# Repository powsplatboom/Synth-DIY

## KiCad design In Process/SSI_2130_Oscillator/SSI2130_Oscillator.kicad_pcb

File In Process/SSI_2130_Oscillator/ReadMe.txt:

VCO based on the SSI 2130 by sound semiconductor. Not yet spun, will update when the board has been spun.

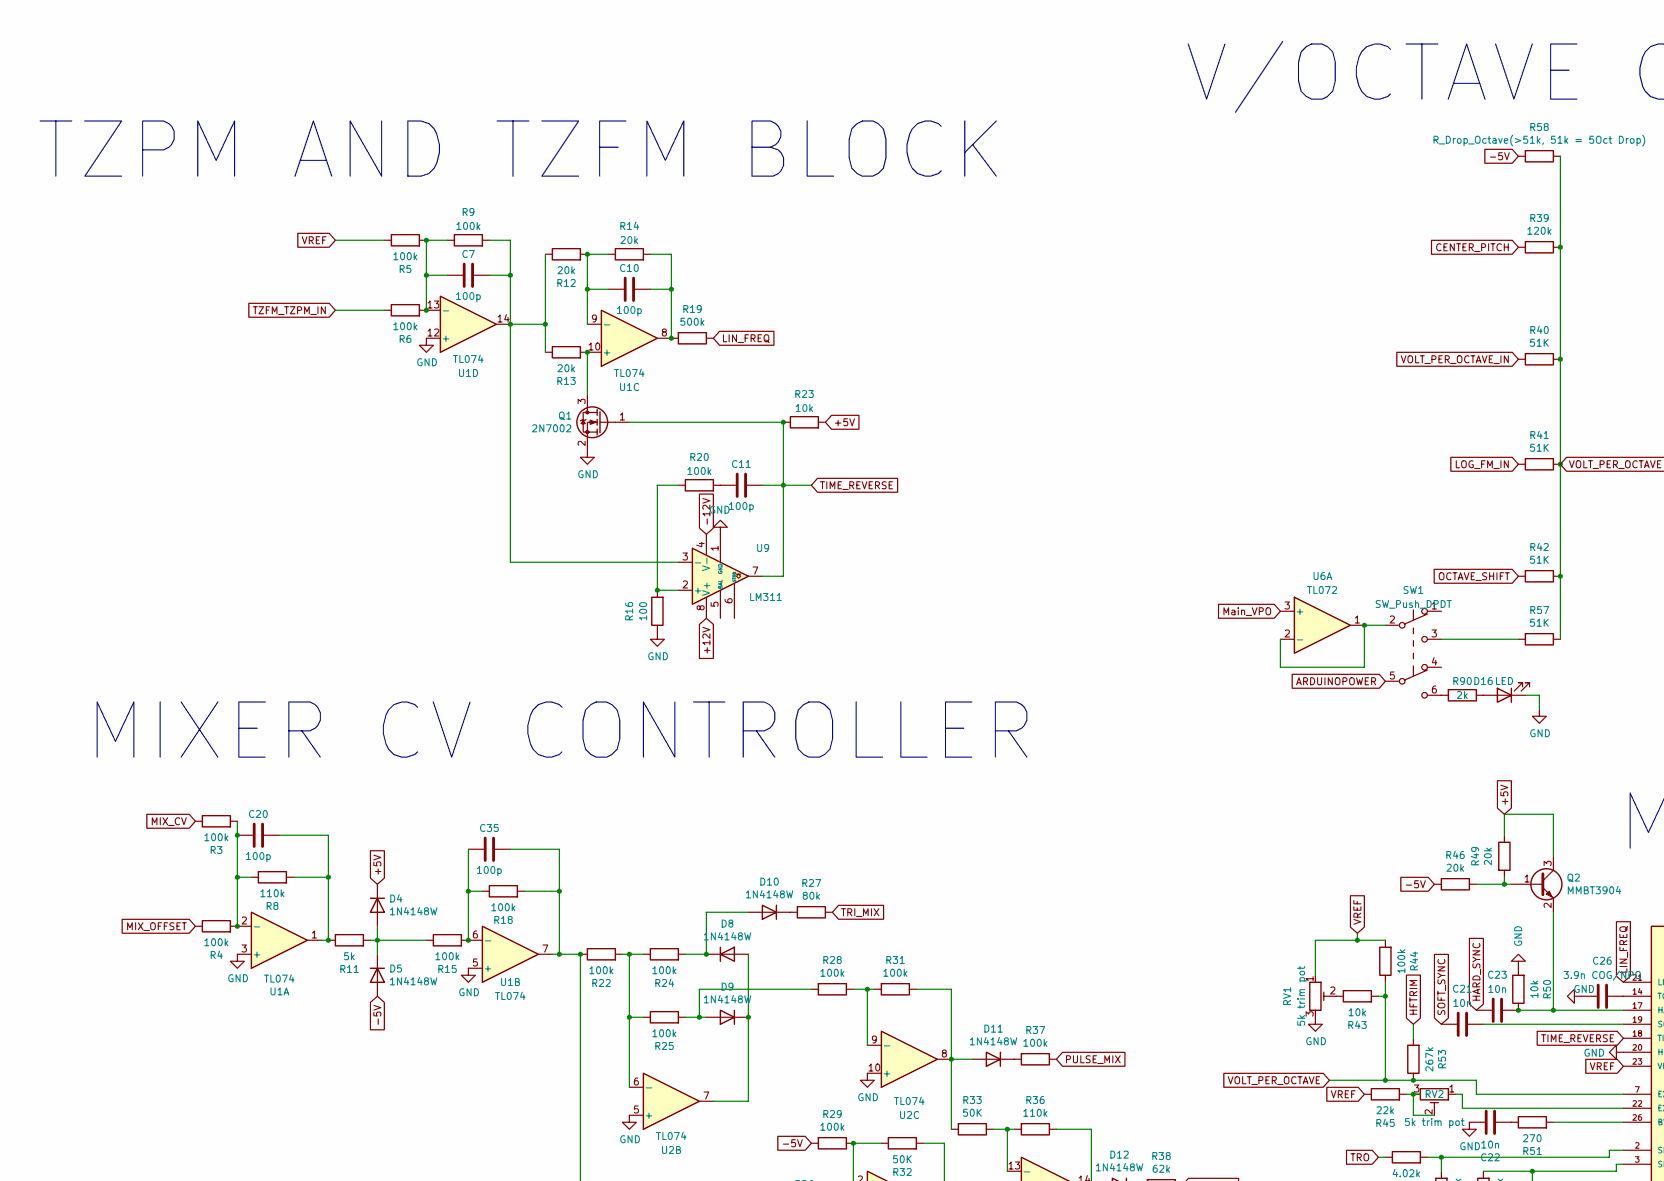
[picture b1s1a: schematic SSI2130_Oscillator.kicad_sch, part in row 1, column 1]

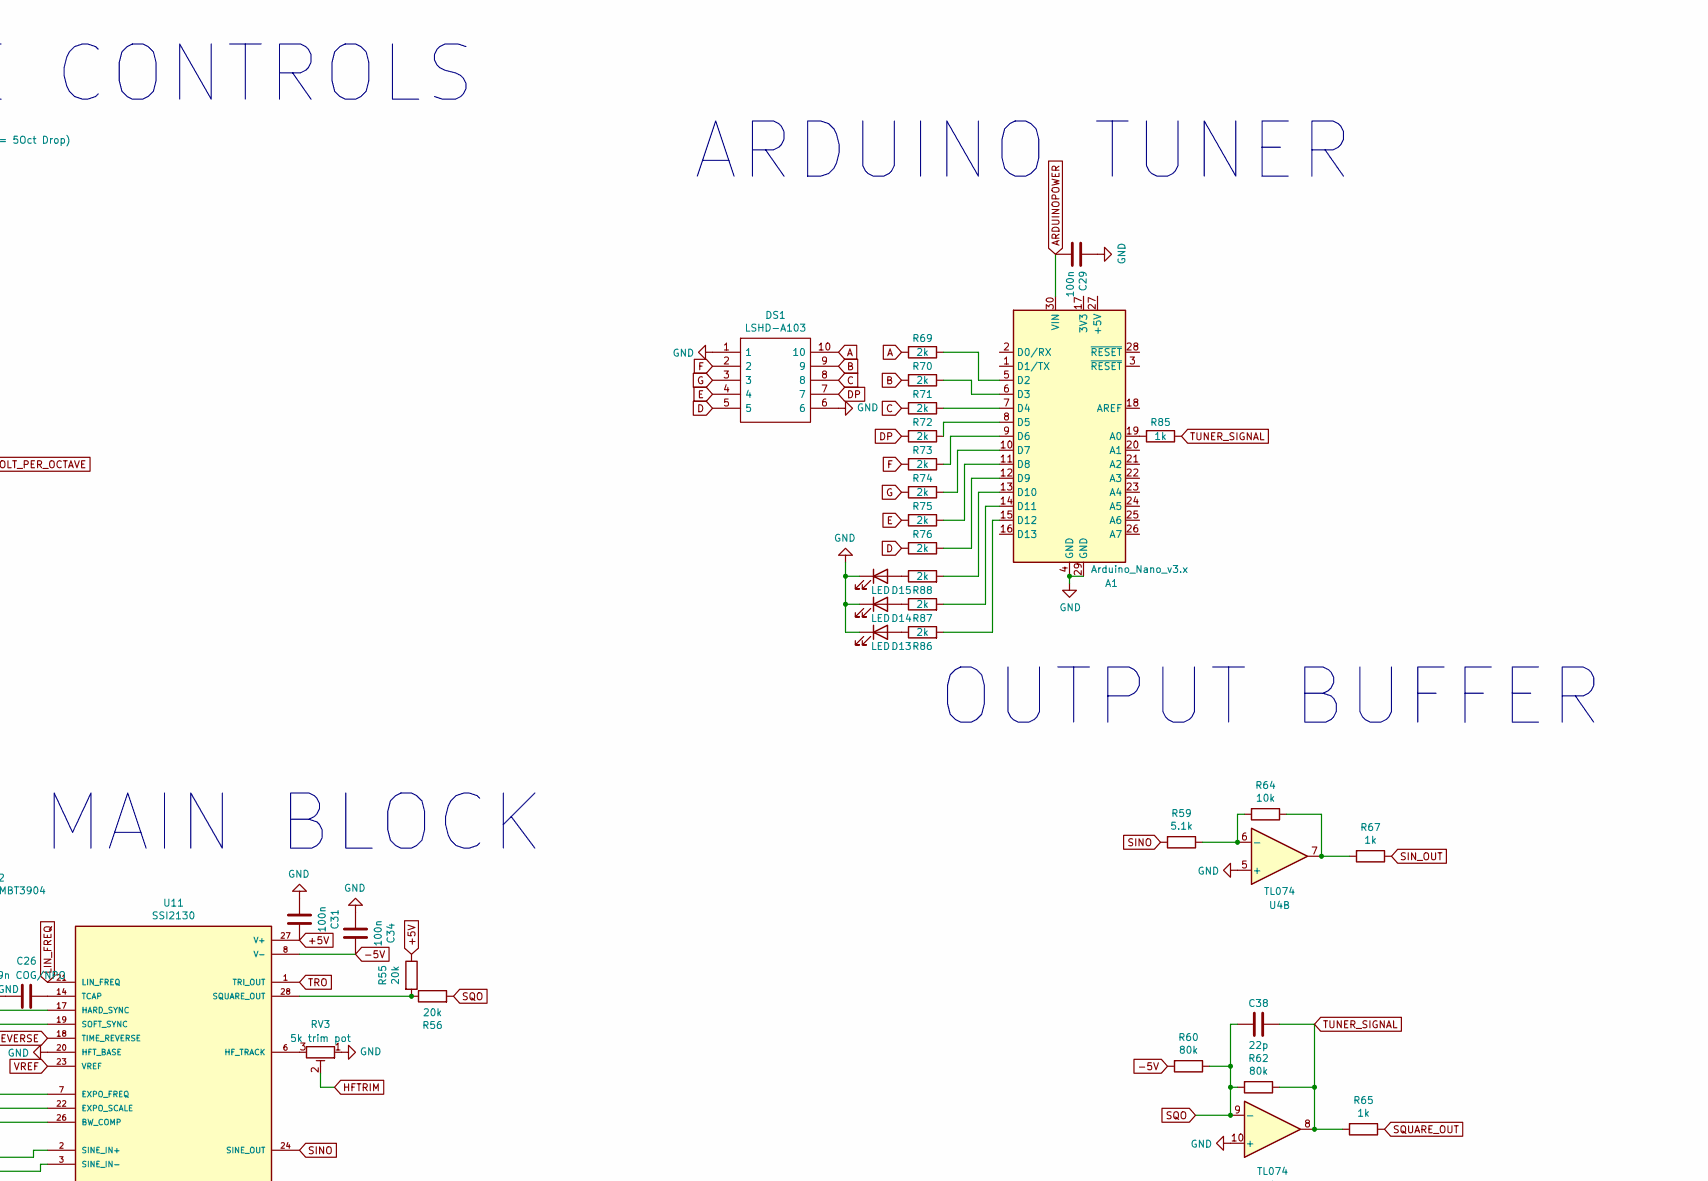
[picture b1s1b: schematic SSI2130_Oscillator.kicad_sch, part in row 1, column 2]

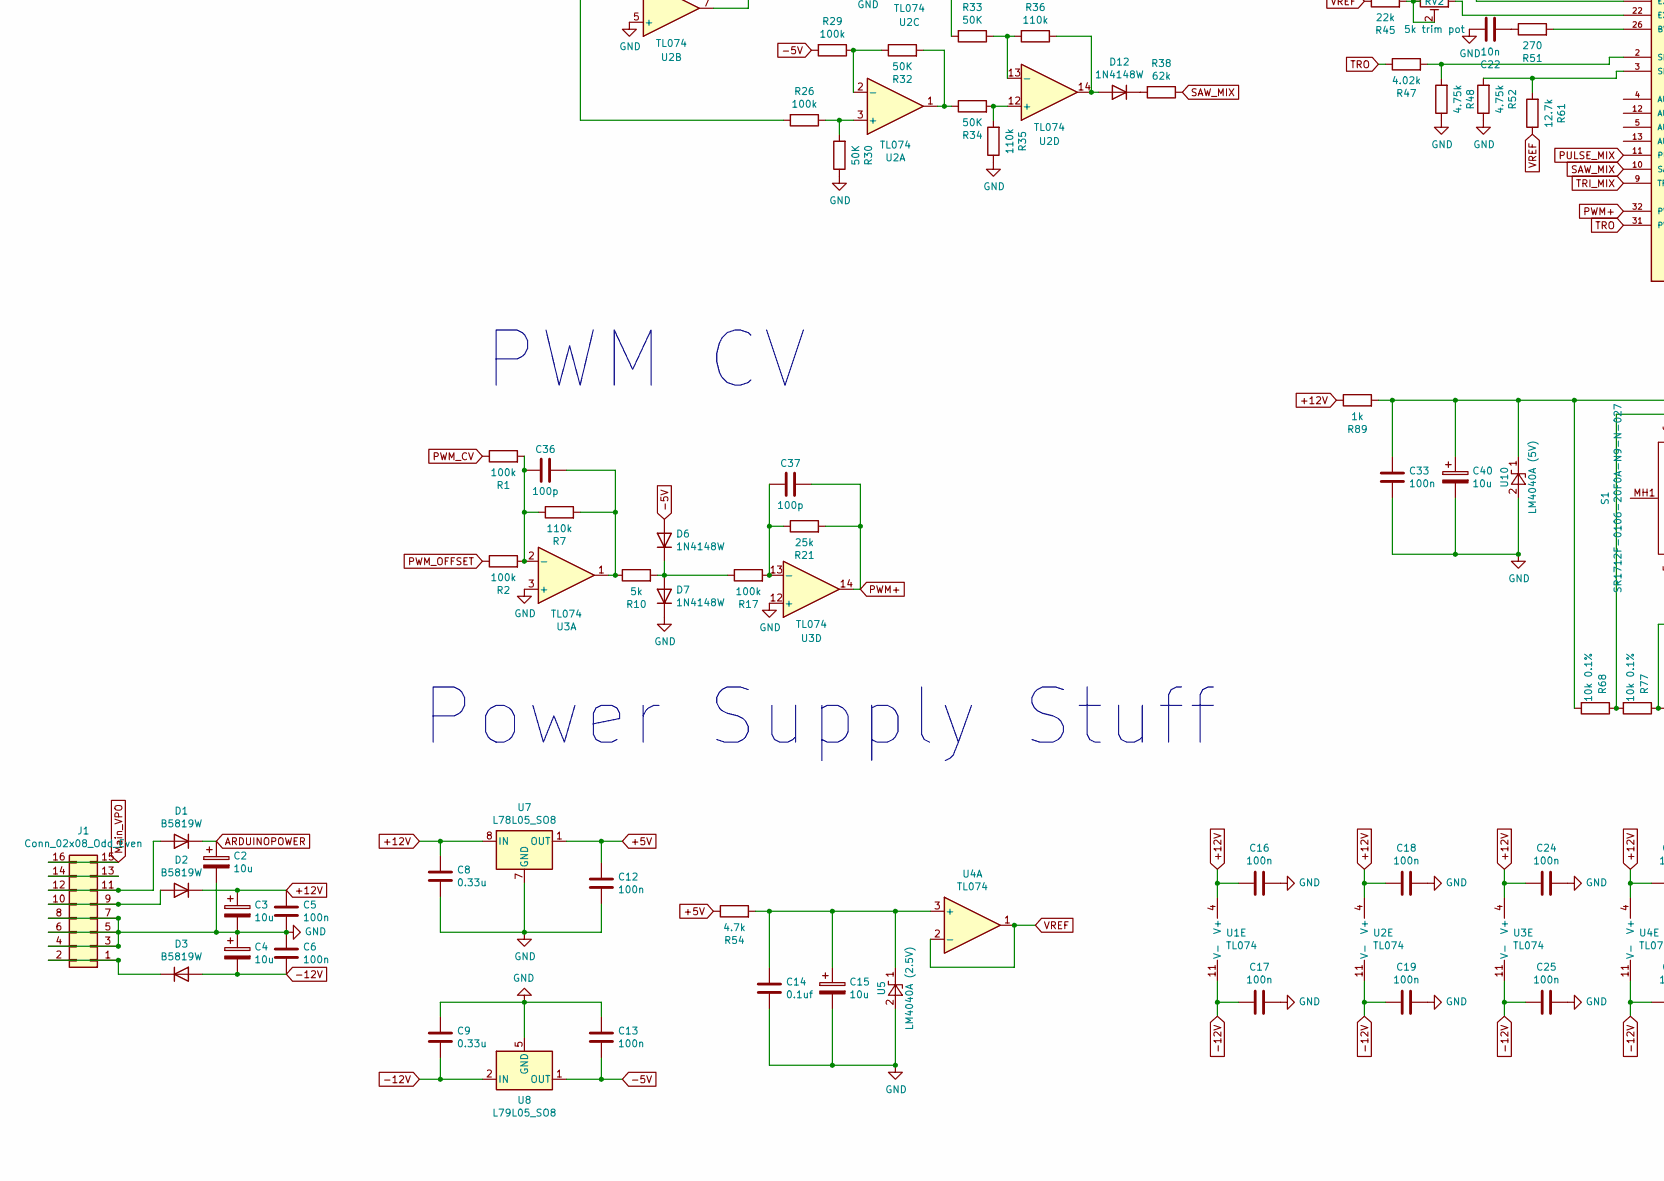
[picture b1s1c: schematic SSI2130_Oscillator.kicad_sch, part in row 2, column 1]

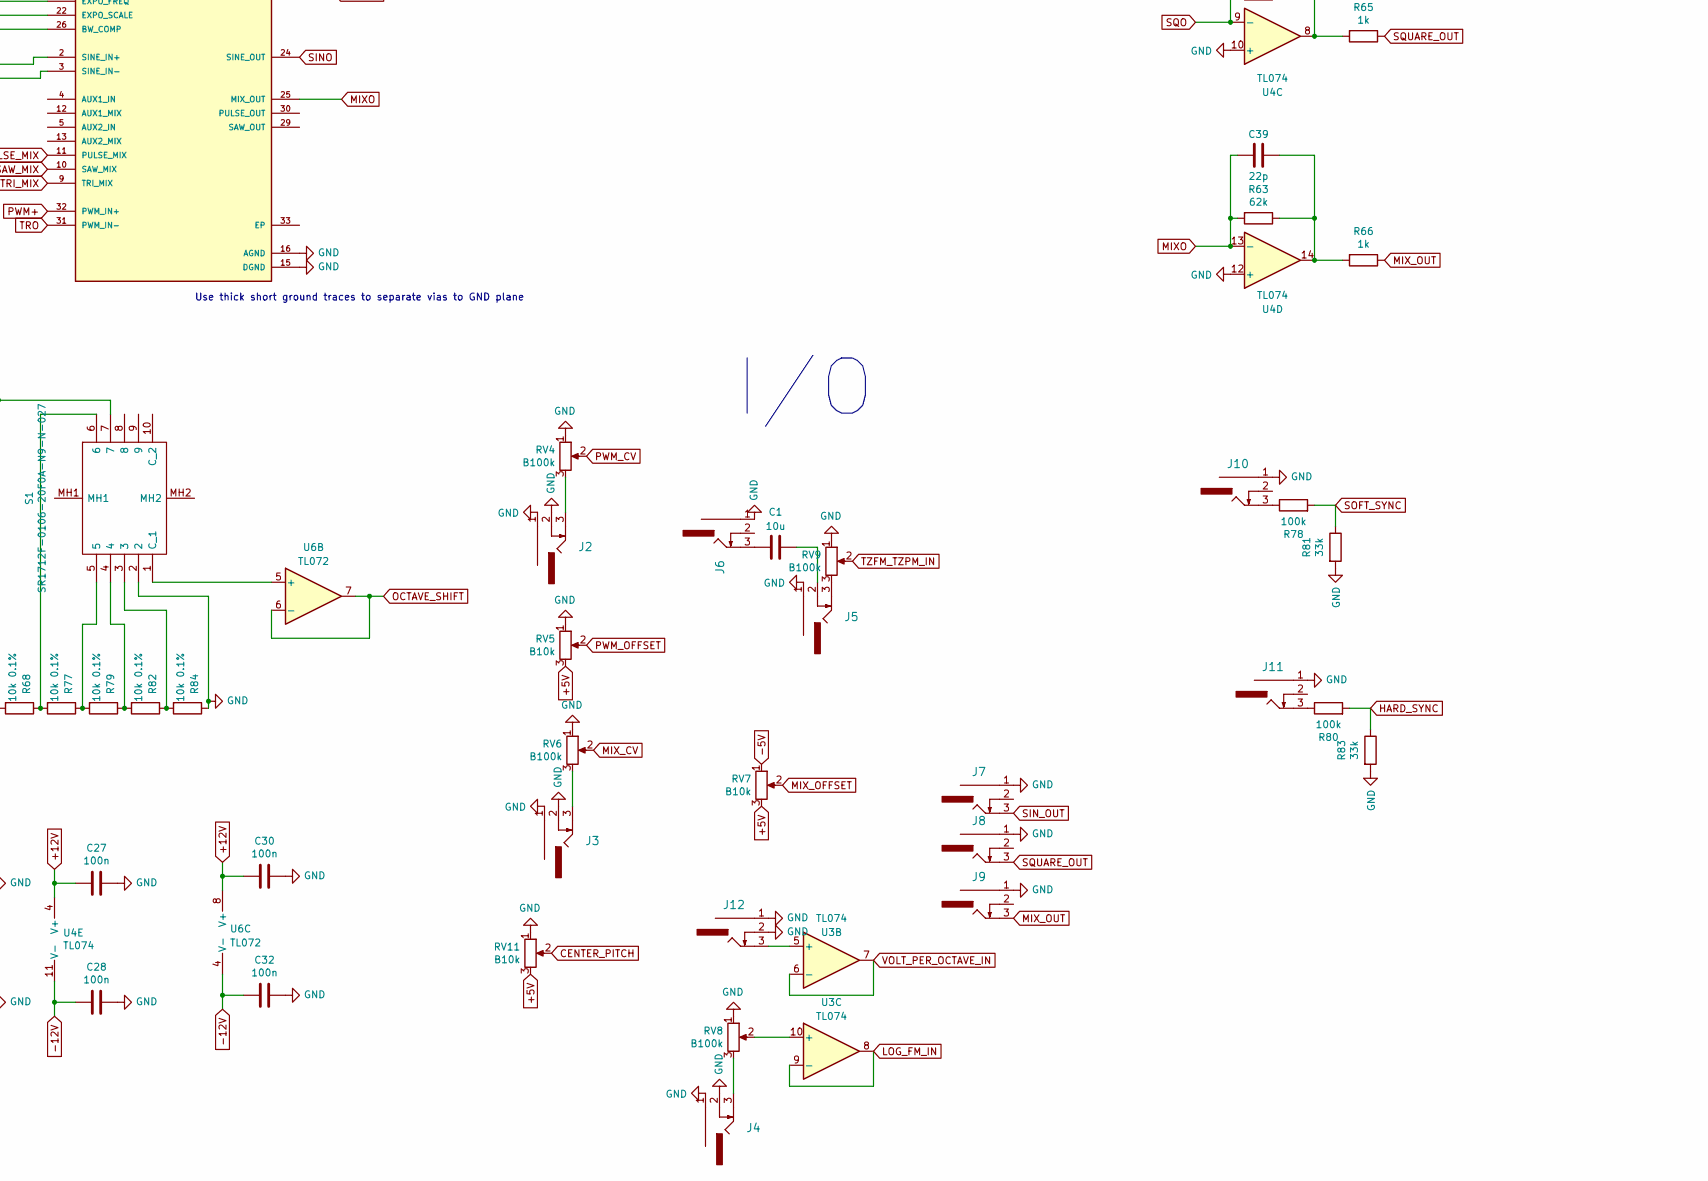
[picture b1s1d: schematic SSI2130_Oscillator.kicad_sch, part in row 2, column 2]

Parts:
A1: Arduino_Nano_v3.x; Arduino_Nano
C1: 10u; C_0603_1608Metric
C2, C3, C4, C15, C40: 10u; CP_Elec_4x5.3
C5, C6, C12, C13, C16, C17, C18, C19, C24, C25, C27, C28, C29, C30, C31, C32, C33, C34: 100n; C_0603_1608Metric
C7, C10, C11, C20, C35, C36, C37: 100p; C_0603_1608Metric
C8, C9: 0.33u; C_0603_1608Metric
C14: 0.1uf; C_0603_1608Metric
C21, C22, C23: 10n; C_0603_1608Metric
C26: 3.9n COG/NPO; C_0603_1608Metric
C38, C39: 22p; C_0603_1608Metric
D1, D2, D3: B5819W; D_SOD-123
D4, D5, D6, D7, D8, D9, D10, D11, D12: 1N4148W; D_SOD-123
D13, D14, D15, D16: LED; LED_0805_2012Metric
DS1: LSHD-A103; DIPS508W50P254L1270H609Q10N; Manufacturer_Part_Number LSHD-A101; Mouser Part Number 859-LSHD-A101
J1: Conn_02x08_Odd_Even; IDC-Header_2x08_P2.54mm_Vertical
J2, J3, J4, J5, J6, J7, J8, J9, J10, J11, J12: PJ301_THONKICONN; PJ-3001_Mono_Phone
Q1: 2N7002; SOT-23
Q2: MMBT3904; SOT-23
R1, R2, R3, R4, R5, R6, R9, R15, R17, R18, R20, R22, R24, R25, R26, R28, R29, R31, R37, R44, R78, R80: 100k; R_0603_1608Metric
R7, R8, R35, R36: 110k; R_0603_1608Metric
R10, R11: 5k; R_0603_1608Metric
R12, R13, R14, R46, R49, R55, R56: 20k; R_0603_1608Metric
R16: 100; R_0603_1608Metric
R19: 500k; R_0603_1608Metric
R21: 25k; R_0603_1608Metric
R23, R43, R50, R64: 10k; R_0603_1608Metric
R27, R60, R62: 80k; R_0603_1608Metric
R30, R32, R33, R34: 50K; R_0603_1608Metric
R38, R63: 62k; R_0603_1608Metric
R39: 120k; R_0603_1608Metric
R40, R41, R42, R57: 51K; R_0603_1608Metric
R45: 22k; R_0603_1608Metric
R47: 4.02k; R_0603_1608Metric
R48, R52: 4.75k; R_0603_1608Metric
R51: 270; R_0603_1608Metric
R53: 267k; R_0603_1608Metric
R54: 4.7k; R_0603_1608Metric
R58: R_Drop_Octave(>51k, 51k = 5Oct Drop); R_0603_1608Metric
R59: 5.1k; R_0603_1608Metric
R61: 12.7k; R_0603_1608Metric
R65, R66, R67, R85, R89: 1k; R_0603_1608Metric
R68, R77, R79, R82, R84: 10k 0.1%; R_0603_1608Metric
R69, R70, R71, R72, R73, R74, R75, R76, R86, R87, R88, R90: 2k; R_0603_1608Metric
R81, R83: 33k; R_0603_1608Metric
RV1, RV2, RV3: 5k trim pot; Potentiometer_Bourns_3296W_Vertical
RV4, RV6, RV8, RV9: B100k; Potentiometer_Alpha_RD901F-40-00D_Single_Vertical
RV5, RV7, RV11: B10k; Potentiometer_Alpha_RD901F-40-00D_Single_Vertical
S1: SR1712F-0106-20F0A-N9-N-027; SR1712F010620F0AN9N027; Manufacturer_Part_Number SR1712F-0106-20F0A-N9-N-027; Mouser Part Number 105-SR1712F-16NS
SW1: SW_Push_DPDT; DPDT Tayda Push Switch
U1, U2, U3, U4: TL074; SOIC-14_3.9x8.7mm_P1.27mm
U5: LM4040A (2.5V); SOT-23
U6: TL072; SO-8_3.9x4.9mm_P1.27mm
U7: L78L05_SO8; SOIC-8_3.9x4.9mm_P1.27mm
U8: L79L05_SO8; SOIC-8_3.9x4.9mm_P1.27mm
U9: LM311; SOIC-8_3.9x4.9mm_P1.27mm
U10: LM4040A (5V); SOT-23
U11: SSI2130; QFN-32-1EP_4x4mm_P0.4mm_EP2.9x2.9mm; PARTREV Rev. 2.4

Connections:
+5V: C12.1, C31.1, D4.1 (K), Q2.3 (C), R23.2, R49.1, R54.1, R55.1, RV5.3, RV7.3, RV11.3, U7.1 (OUT), U11.27 (V+)
+12V: C3.1, C5.1, C8.1, C16.2, C18.2, C24.2, C27.2, C30.2, D2.1 (K), R89.1, U1.4 (V+), U2.4 (V+), U3.4 (V+), U4.4 (V+), U6.8 (V+), U7.8 (IN), U9.8 (V+)
-5V: C13.2, C34.1, D5.2 (A), D6.2 (A), R29.2, R46.2, R58.2, R60.2, RV7.1, U8.1 (OUT), U11.8 (V-)
-12V: C4.2, C6.2, C9.2, C17.2, C19.2, C25.2, C28.2, C32.2, D3.2 (A), U1.11 (V-), U2.11 (V-), U3.11 (V-), U4.11 (V-), U6.4 (V-), U8.2 (IN), U8.3 (IN), U8.6 (IN), U8.7 (IN), U9.4 (V-)
A: DS1.10, R69.2
ARDUINOPOWER: A1.30 (VIN), C2.1, C29.2, D1.1 (K), SW1.5 (B)
B: DS1.9, R70.2
C: DS1.8, R71.2
CENTER_PITCH: R39.2, RV11.2
D: DS1.5, R76.2
DP: DS1.7, R72.2
E: DS1.4, R75.2
F: DS1.2, R73.2
G: DS1.3, R74.2
GND: A1.4 (GND), A1.29 (GND), C2.2, C3.2, C4.1, C5.2, C6.1, C8.2, C9.1, C12.2, C13.1, C14.2, C15.2, C16.1, C17.1, C18.1, C19.1, C22.1, C24.1, C25.1, C26.2, C27.1, C28.1, C29.1, C30.1, C31.2, C32.1, C33.2, C34.2, C40.2, D7.1 (K), D13.1 (K), D14.1 (K), D15.1 (K), D16.1 (K), DS1.1, DS1.6, J1.3, J1.4, J1.5, J1.6, J1.7, J1.8, J2.1, J2.2, J3.1, J3.2, J4.1, J4.2, J5.1, J6.1, J7.1, J8.1, J9.1, J10.1, J11.1, J12.1, J12.2, Q1.2 (S), R16.1, R30.1, R35.1, R48.1, R50.2, R52.1, R81.2, R83.2, R84.1, RV1.3, RV3.1, RV4.1, RV5.1, RV6.1, RV8.1, RV9.1, RV11.1, S1.2, U1.3 (+), U1.5 (+), U1.12 (+), U2.5 (+), U2.10 (+), U3.3 (+), U3.12 (+), U4.5 (+), U4.10 (+), U4.12 (+), U5.2 (A), U7.2 (GND), U7.3 (GND), U7.6 (GND), U7.7 (GND), U8.5 (GND), U9.1 (GND), U10.2 (A), U11.15 (DGND), U11.16 (AGND), U11.20 (HFT_BASE)
HARD_SYNC: C23.2, R80.2, R83.1
HFTRIM: R53.2, RV3.2
LIN_FREQ: R19.1, U11.21 (LIN_FREQ)
LOG_FM_IN: R41.2, U3.8, U3.9 (-)
MIXO: C39.2, R63.2, U4.13 (-), U11.25 (MIX_OUT)
MIX_CV: R3.1, RV6.2
MIX_OFFSET: R4.1, RV7.2
MIX_OUT: J9.3, R66.1
Main_VPO: J1.15, J1.16, U6.3 (+)
unnamed: A1.19 (A0), R85.2
unnamed: A1.5 (D2), R69.1
unnamed: A1.6 (D3), R70.1
unnamed: A1.7 (D4), R71.1
unnamed: A1.8 (D5), R72.1
unnamed: A1.9 (D6), R73.1
unnamed: A1.10 (D7), R74.1
unnamed: A1.11 (D8), R75.1
unnamed: A1.12 (D9), R76.1
unnamed: A1.13 (D10), R88.2
unnamed: A1.14 (D11), R87.2
unnamed: A1.15 (D12), R86.2
unnamed: C1.1, J5.2
unnamed: C1.2, J6.3
unnamed: C10.1, R14.2, R19.2, U1.8
unnamed: C11.2, R20.2
unnamed: C20.1, R8.2, R11.1, U1.1
unnamed: C22.2, R51.1
unnamed: C35.1, R18.2, R22.1, R26.2, U1.7
unnamed: C36.1, R7.2, R10.1, U3.1
unnamed: C39.1, R63.1, R66.2, U4.14
unnamed: D1.2 (A), J1.11, J1.12
unnamed: D2.2 (A), J1.9, J1.10
unnamed: D3.1 (K), J1.1, J1.2
unnamed: D4.2 (A), D5.1 (K), R11.2, R15.1
unnamed: D6.1 (K), D7.2 (A), R10.2, R17.1
unnamed: D8.2 (A), D9.1 (K), U2.7
unnamed: D9.2 (A), R25.2, R28.2
unnamed: D8.1 (K), D10.2 (A), R24.2
unnamed: D10.1 (K), R27.2
unnamed: D11.2 (A), R31.1, R33.2, U2.8
unnamed: D11.1 (K), R37.2
unnamed: D12.2 (A), R36.1, U2.14
unnamed: D12.1 (K), R38.2
unnamed: D13.2 (A), R86.1
unnamed: D14.2 (A), R87.1
unnamed: D15.2 (A), R88.1
unnamed: D16.2 (A), R90.1
unnamed: J1.13, J1.14
unnamed: J2.3, RV4.3
unnamed: J3.3, RV6.3
unnamed: J4.3, RV8.3
unnamed: J5.3, RV9.3
unnamed: J10.3, R78.1
unnamed: J11.3, R80.1
unnamed: Q1.3 (D), R13.2, U1.10 (+)
unnamed: Q2.1 (B), R46.1, R49.2
unnamed: C23.1, Q2.2 (E), R50.1, U11.17 (HARD_SYNC)
unnamed: R32.2, R34.1, U2.1
unnamed: R43.1, RV1.2
unnamed: R45.2, RV2.2, RV2.3
unnamed: R57.2, SW1.3 (C)
unnamed: R64.1, R67.2, U4.7
unnamed: R68.1, R77.2, S1.6
unnamed: R77.1, R79.2, S1.5
unnamed: R79.1, R82.2, S1.4
unnamed: R82.1, R84.2, S1.3
unnamed: R90.2, SW1.6 (C)
unnamed: S1.1 (C_1), U6.5 (+)
unnamed: C20.2, R3.2, R4.2, R8.1, U1.2 (-)
unnamed: C35.2, R15.2, R18.1, U1.6 (-)
unnamed: C10.2, R12.2, R14.1, U1.9 (-)
unnamed: C7.2, R5.2, R6.2, R9.1, U1.13 (-)
unnamed: R26.1, R30.2, U2.3 (+)
unnamed: R29.1, R32.1, U2.2 (-)
unnamed: R22.2, R24.1, R25.1, U2.6 (-)
unnamed: R28.1, R31.2, U2.9 (-)
unnamed: R34.2, R35.2, U2.12 (+)
unnamed: R33.1, R36.2, U2.13 (-)
unnamed: C36.2, R1.2, R2.2, R7.1, U3.2 (-)
unnamed: J12.3, U3.5 (+)
unnamed: RV8.2, U3.10 (+)
unnamed: C37.2, R17.2, R21.1, U3.13 (-)
unnamed: C14.1, C15.1, R54.2, U4.3 (+), U5.1 (K)
unnamed: R59.1, R64.2, U4.6 (-)
unnamed: SW1.2 (B), U6.1, U6.2 (-)
unnamed: R16.2, R20.1, U9.2 (+)
unnamed: C7.1, R9.2, R12.1, R13.1, U1.14, U9.3 (-)
unnamed: C33.1, C40.1, R68.2, R89.2, S1.7, U10.1 (K)
unnamed: R51.2, U11.26 (BW_COMP)
unnamed: RV2.1, U11.22 (EXPO_SCALE)
unnamed: RV3.3, U11.6 (HF_TRACK)
unnamed: R47.2, R48.2, U11.2 (SINE_IN+)
unnamed: R52.2, R61.2, U11.3 (SINE_IN-)
unnamed: C21.1, U11.19 (SOFT_SYNC)
unnamed: R55.2, R56.1, U11.28 (SQUARE_OUT)
unnamed: C26.1, U11.14 (TCAP)
OCTAVE_SHIFT: R42.2, U6.6 (-), U6.7
PULSE_MIX: R37.1, U11.11 (PULSE_MIX)
PWM+: C37.1, R21.2, U3.14, U11.32 (PWM_IN+)
PWM_CV: R1.1, RV4.2
PWM_OFFSET: R2.1, RV5.2
SAW_MIX: R38.1, U11.10 (SAW_MIX)
SINO: R59.2, U11.24 (SINE_OUT)
SIN_OUT: J7.3, R67.1
SOFT_SYNC: C21.2, R78.2, R81.1
SQO: C38.2, R56.2, R60.1, R62.2, U4.9 (-)
SQUARE_OUT: J8.3, R65.1
TIME_REVERSE: C11.1, Q1.1 (G), R23.1, U9.7, U11.18 (TIME_REVERSE)
TRI_MIX: R27.1, U11.9 (TRI_MIX)
TRO: R47.1, U11.1 (TRI_OUT), U11.31 (PWM_IN-)
TUNER_SIGNAL: C38.1, R62.1, R65.2, R85.1, U4.8
TZFM_TZPM_IN: R6.1, RV9.2
VOLT_PER_OCTAVE: R39.1, R40.1, R41.1, R42.1, R43.2, R44.1, R53.1, R57.1, R58.1, U11.7 (EXPO_FREQ)
VOLT_PER_OCTAVE_IN: R40.2, U3.6 (-), U3.7
VREF: R5.1, R44.2, R45.1, R61.1, RV1.1, U4.1, U4.2 (-), U11.23 (VREF)

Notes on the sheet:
MIXER CV CONTROLLER
OUTPUT BUFFER
TZPM AND TZFM BLOCK
PWM CV
I/O
MAIN BLOCK
ARDUINO TUNER
Power Supply Stuff
V/OCTAVE CONTROLS
Use thick short ground traces to separate vias to GND plane

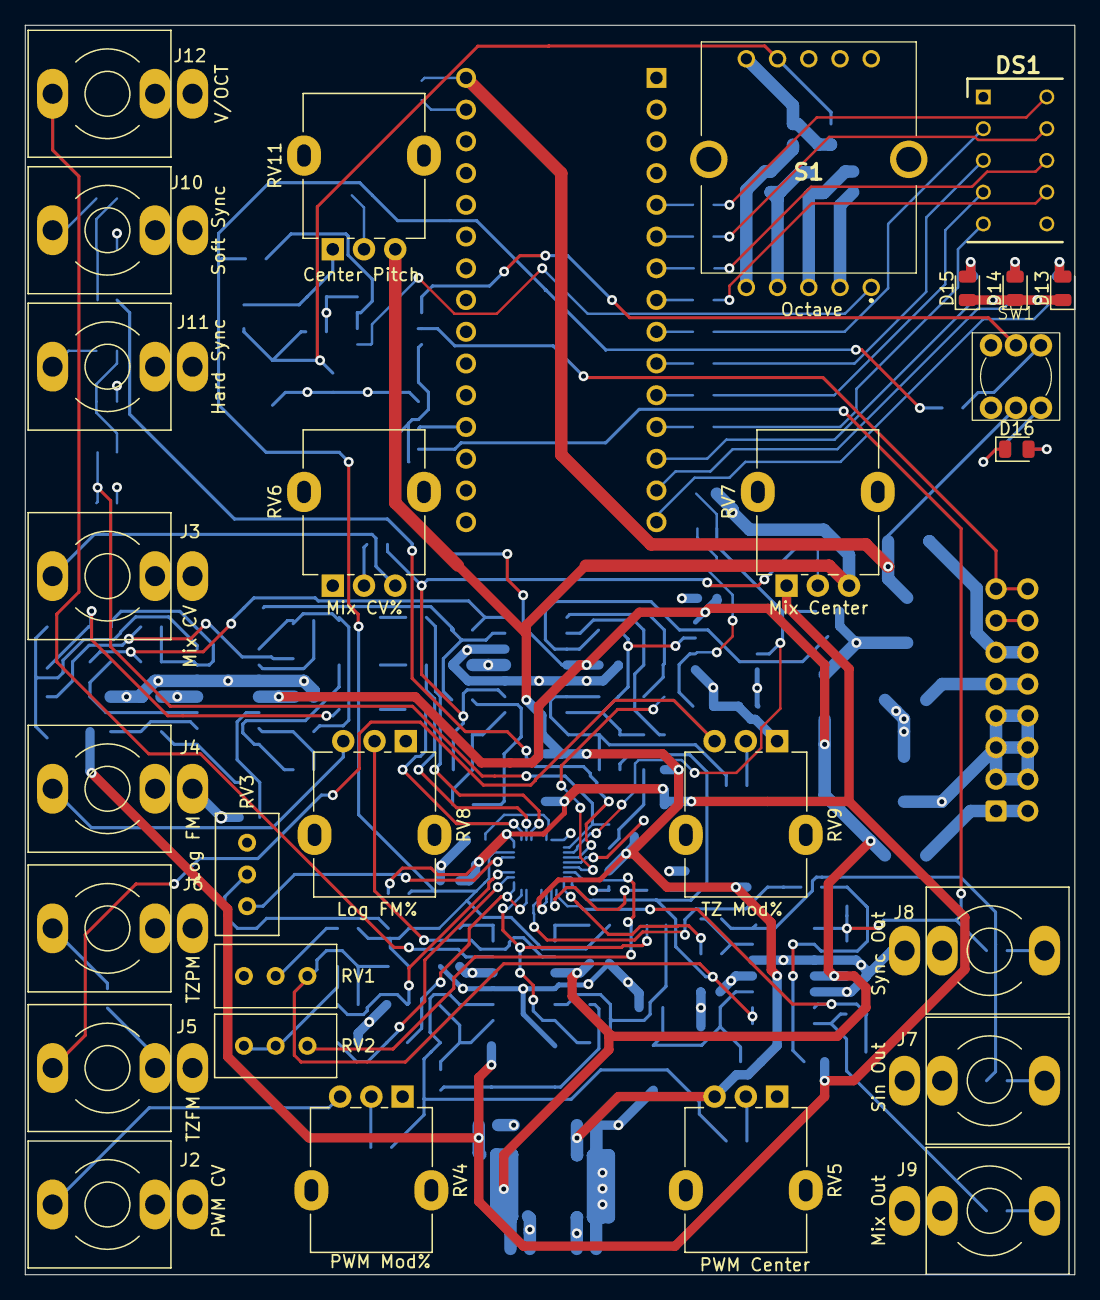
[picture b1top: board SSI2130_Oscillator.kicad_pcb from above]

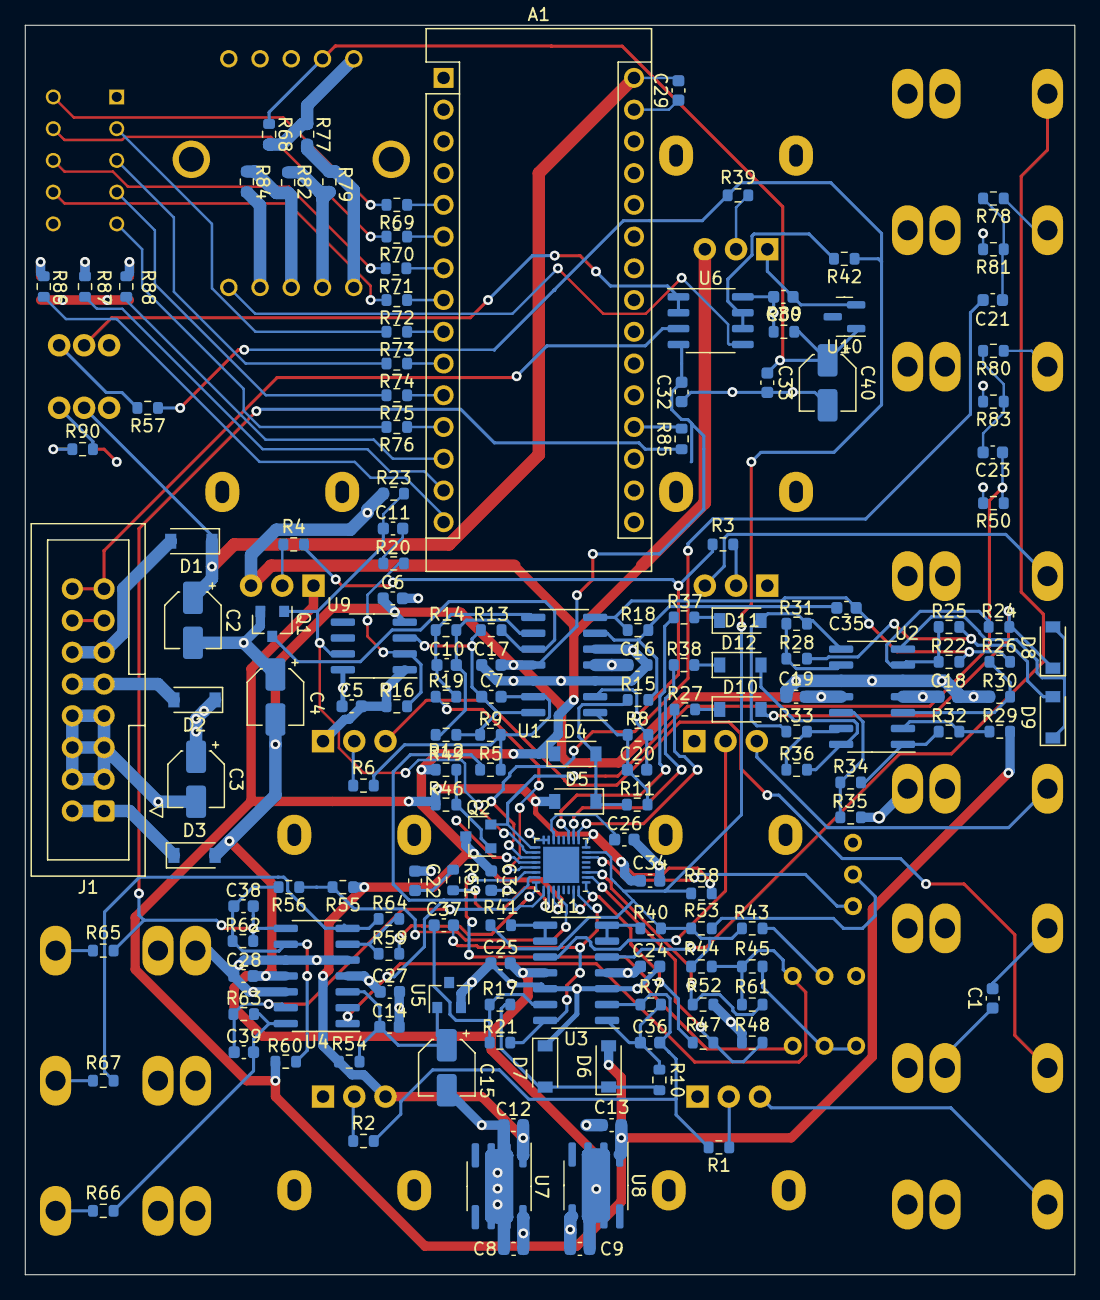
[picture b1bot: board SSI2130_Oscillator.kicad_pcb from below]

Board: 4 copper layers, 84.0 x 100.0 mm, 185 parts (157 on the bottom side), 130 nets.
